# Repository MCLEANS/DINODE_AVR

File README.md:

# DINODE-AVR
An IOT development board based on ATMEGA32-16AU
        
        ATMEGA32-16AU DATASHEET
        http://ww1.microchip.com/downloads/en/devicedoc/doc2503.pdf

## BACKGROUND
The DINODE-AVR dev board comes out of the TU-K DATA open source project started by JACK MCLEANS and STEVE KIBUIKA from the Technical University of Kenya.
The project is intended to build a central database based on MongoDB with an API to insert data into and take data out of. 
The Central database is  to contain data from different IoT sensors from around the campus deployed by the students during their personal or final year projects.
By obtaining an API Key the various sensor data can be pushed to the database.
Projects that require data to implement such as Machine Learning and Data Visualization can also request for data from the "Data pool" and easily use it for their projects.

## CHALLENGE
A challenge arises where most of the students who do not have a hardware background or are just starting out do not have access to cheap internet enabled dev boards to start off.
Most of the available Internet Based Dev-boards are expensive or an option of modules such as WIFI and GSM which have "HARD" power requirements that are not easy for a beginer.
Most projects are also arduino based making students rely of third party libraries and abstracting them from the hardware. Arduino boards are also not suitable for realtime applicaions.

## Solution

As from the above challenges the DINODE-AVR was born, We decided to develop a Dev board based on the ATMEGA32 micro-controller with WIFI(ESP8266) and GSM connections already done,making in a plug and play for IoT one level lower than the ARDUINO to enable understanding of how the different IoT protocols work.

## VISION
To have more students get into Embedded systems and IoT development with a firm understanding of the basics.

# DINODE-AVR DEV-BOARD
The development board comes with an inbuilt user-led, user-potentiometer as well as "plug and play" sockets for LCD screen, ESP8266 and GSM SIM800L V2.0 to aid in IoT projects.

## LCD SCREEN PIN CONNECTIONS

        LCD       DINODE-AVR
        RS          PB0
        RW          PB1
        E           PB2
        D0          PC0
        D1          PC1
        D2          PC2
        D3          PC3
        D4          PC4
        D5          PC5
        D6          PC6
        D7          PC7
        A           +5V
        K           GND
        VSS         GND
        VDD         +5V

## USER-LED
The inbuilt USER-LED is connected to pin PD7 of the DINODE-AVR with a current limmiting resistor of 220 ohms

## USER-POTENTIOMETER
The user potentiometer is connected to pin PA0 of the DINODE-AVR

## ESP8266 CONNECTION

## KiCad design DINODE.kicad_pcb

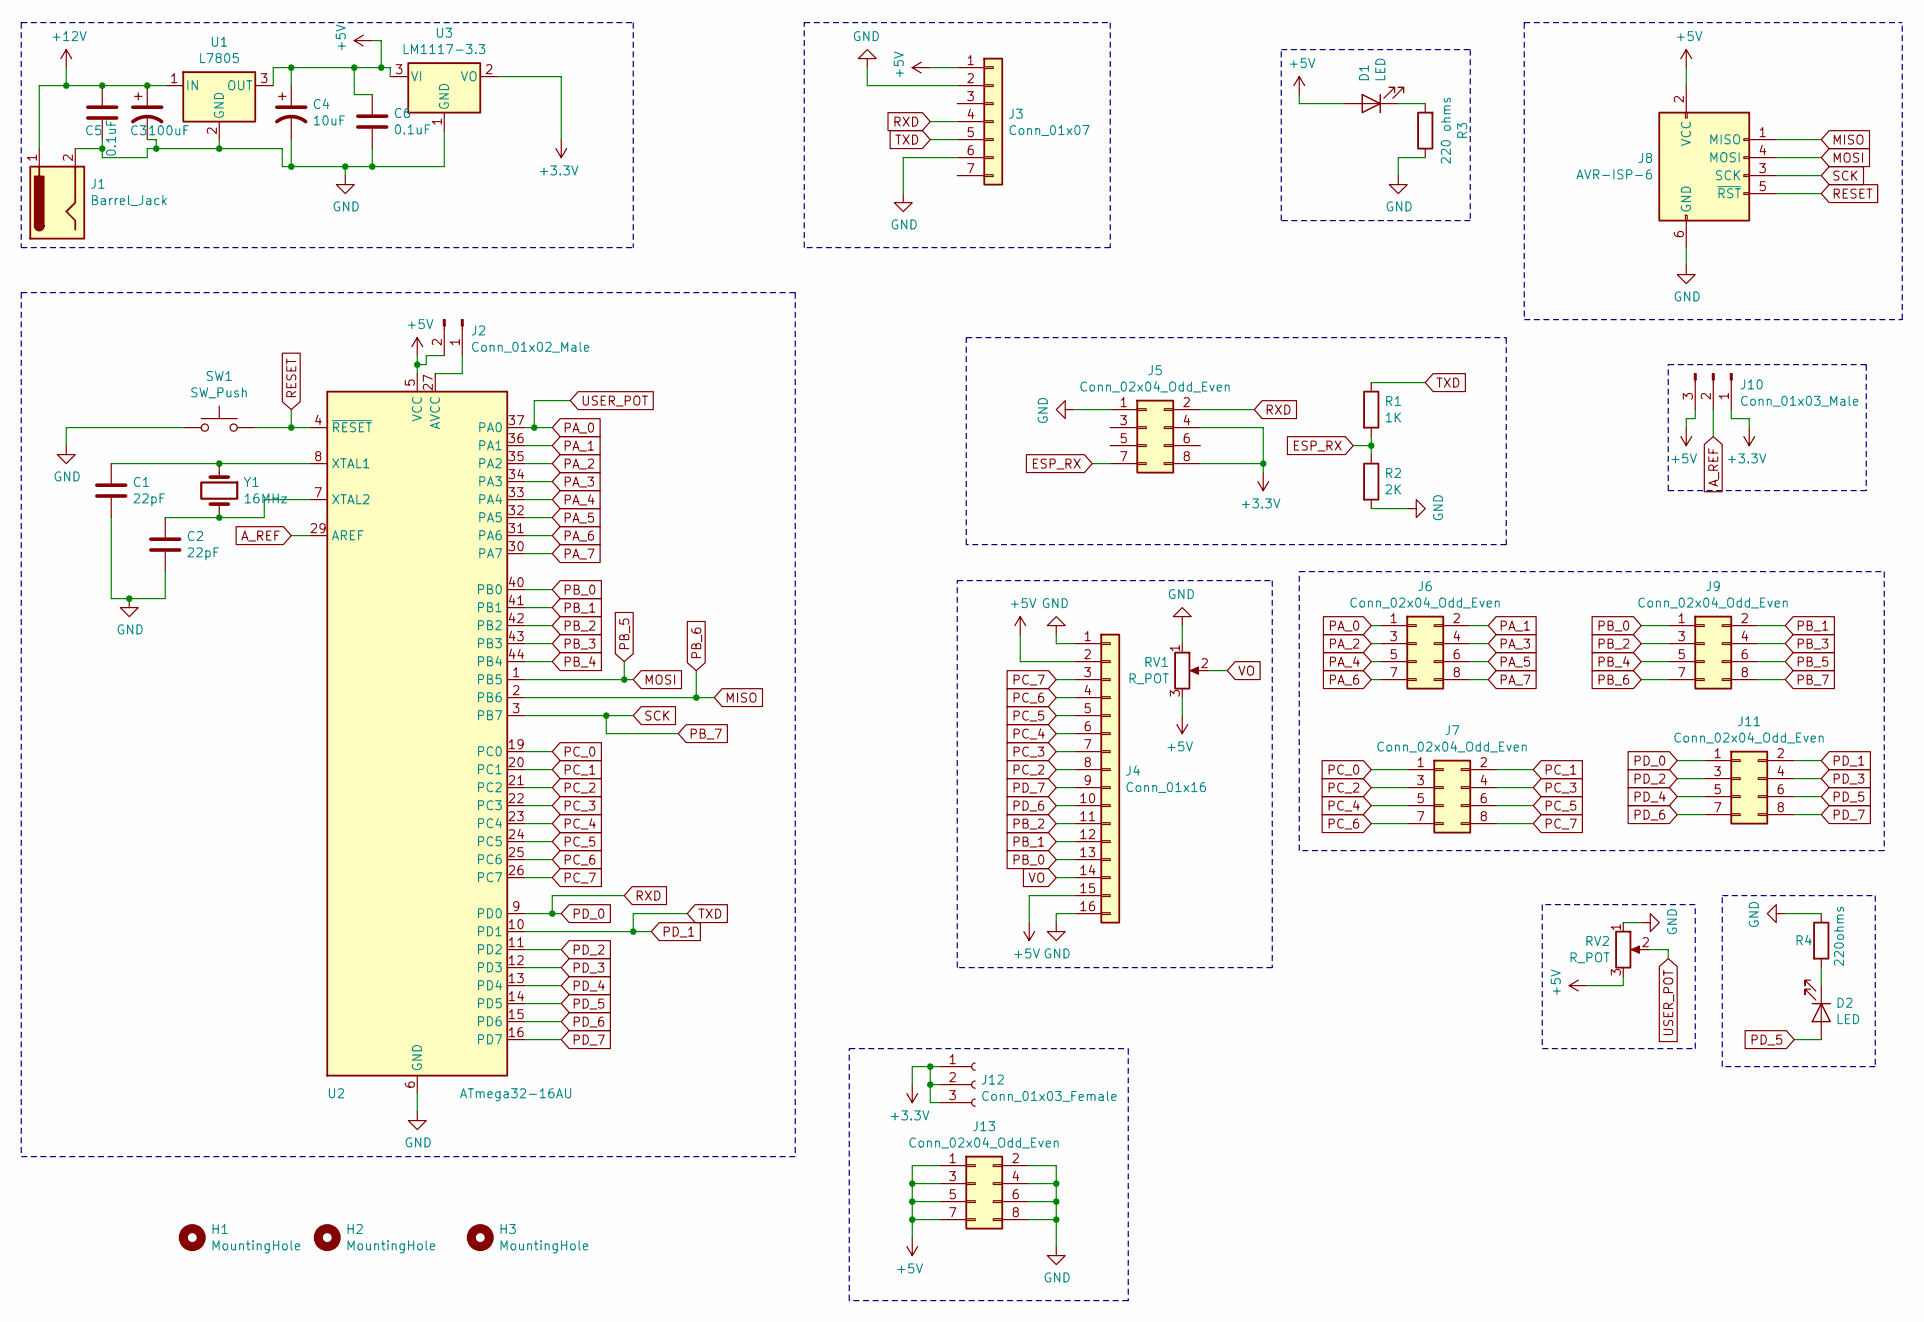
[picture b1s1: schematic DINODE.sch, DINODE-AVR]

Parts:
C1, C2: 22pF; C_0805_2012Metric
C3: 100uF; CP_Radial_D8.0mm_P5.00mm
C4: 10uF; CP_Radial_D8.0mm_P5.00mm
C5, C6: 0.1uF; C_0805_2012Metric
D1, D2: LED; LED_D3.0mm
H1, H2, H3: MountingHole; MountingHole_3.2mm_M3
J1: Barrel_Jack; BarrelJack_Horizontal
J2: Conn_01x02_Male; PinHeader_1x02_P2.54mm_Vertical
J3: Conn_01x07; PinSocket_1x07_P2.54mm_Vertical
J4: Conn_01x16; PinSocket_1x16_P2.54mm_Vertical
J5, J13: Conn_02x04_Odd_Even; PinSocket_2x04_P2.54mm_Vertical
J6, J7, J9, J11: Conn_02x04_Odd_Even; PinHeader_2x04_P2.54mm_Horizontal
J8: AVR-ISP-6; IDC-Header_2x03_P2.54mm_Horizontal
J10: Conn_01x03_Male; PinHeader_1x03_P2.54mm_Vertical
J12: Conn_01x03_Female; PinSocket_1x03_P2.54mm_Vertical
R1: 1K; R_Axial_DIN0207_L6.3mm_D2.5mm_P7.62mm_Horizontal
R2: 2K; R_Axial_DIN0207_L6.3mm_D2.5mm_P7.62mm_Horizontal
R3: 220 ohms; R_0805_2012Metric
R4: 220ohms; R_0805_2012Metric
RV1, RV2: R_POT; Potentiometer_Piher_PT-6-V_Vertical
SW1: SW_Push; SW_PUSH_6mm_H5mm
U1: L7805; TO-220-3
U2: ATmega32-16AU; TQFP-44_10x10mm_P0.8mm
U3: LM1117-3.3; SOT-223
Y1: 16MHz; Crystal_HC49-U_Vertical

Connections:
+3V3: J5.4, J5.8, J10.1, J12.1, J12.2, J12.3, U3.2 (VO)
+5V: C4.1, C6.1, D1.2 (A), J2.2, J3.1, J4.2, J4.15, J8.2 (VCC), J10.3, J13.1, J13.3, J13.5, J13.7, RV1.3, RV2.3, U1.3 (OUT), U2.5 (VCC), U2.17 (VCC), U2.38 (VCC), U3.3 (VI)
+12V: C3.1, C5.1, J1.1, U1.1 (IN)
A_REF: J10.2, U2.29 (AREF)
ESP_RX: J5.7, R1.2, R2.1
GND: C1.2, C2.2, C3.2, C4.2, C5.2, C6.2, J1.2, J3.2, J3.6, J4.1, J4.16, J5.1, J8.6 (GND), J13.2, J13.4, J13.6, J13.8, R2.2, R3.1, R4.1, RV1.1, RV2.1, SW1.1, U1.2 (GND), U2.6 (GND), U2.18 (GND), U2.28 (GND), U2.39 (GND), U3.1 (GND)
MISO: J8.1 (MISO), J9.7, U2.2 (PB6)
MOSI: J8.4 (MOSI), J9.6, U2.1 (PB5)
unnamed: C1.1, U2.8 (XTAL1), Y1.1
unnamed: C2.1, U2.7 (XTAL2), Y1.2
unnamed: D1.1 (K), R3.2
unnamed: D2.1 (K), R4.2
unnamed: J2.1, U2.27 (AVCC)
PA_0: J6.1, RV2.2, U2.37 (PA0)
PA_1: J6.2, U2.36 (PA1)
PA_2: J6.3, U2.35 (PA2)
PA_3: J6.4, U2.34 (PA3)
PA_4: J6.5, U2.33 (PA4)
PA_5: J6.6, U2.32 (PA5)
PA_6: J6.7, U2.31 (PA6)
PA_7: J6.8, U2.30 (PA7)
PB_0: J4.13, J9.1, U2.40 (PB0)
PB_1: J4.12, J9.2, U2.41 (PB1)
PB_2: J4.11, J9.3, U2.42 (PB2)
PB_3: J9.4, U2.43 (PB3)
PB_4: J9.5, U2.44 (PB4)
PB_7: J8.3 (SCK), J9.8, U2.3 (PB7)
PC_0: J7.1, U2.19 (PC0)
PC_1: J7.2, U2.20 (PC1)
PC_2: J4.8, J7.3, U2.21 (PC2)
PC_3: J4.7, J7.4, U2.22 (PC3)
PC_4: J4.6, J7.5, U2.23 (PC4)
PC_5: J4.5, J7.6, U2.24 (PC5)
PC_6: J4.4, J7.7, U2.25 (PC6)
PC_7: J4.3, J7.8, U2.26 (PC7)
PD_0: J3.4, J5.2, J11.1, U2.9 (PD0)
PD_1: J3.5, J11.2, R1.1, U2.10 (PD1)
PD_2: J11.3, U2.11 (PD2)
PD_3: J11.4, U2.12 (PD3)
PD_4: J11.5, U2.13 (PD4)
PD_5: D2.2 (A), J11.6, U2.14 (PD5)
PD_6: J4.10, J11.7, U2.15 (PD6)
PD_7: J4.9, J11.8, U2.16 (PD7)
RESET: J8.5 (~RST), SW1.2, U2.4 (~RESET)
VO: J4.14, RV1.2

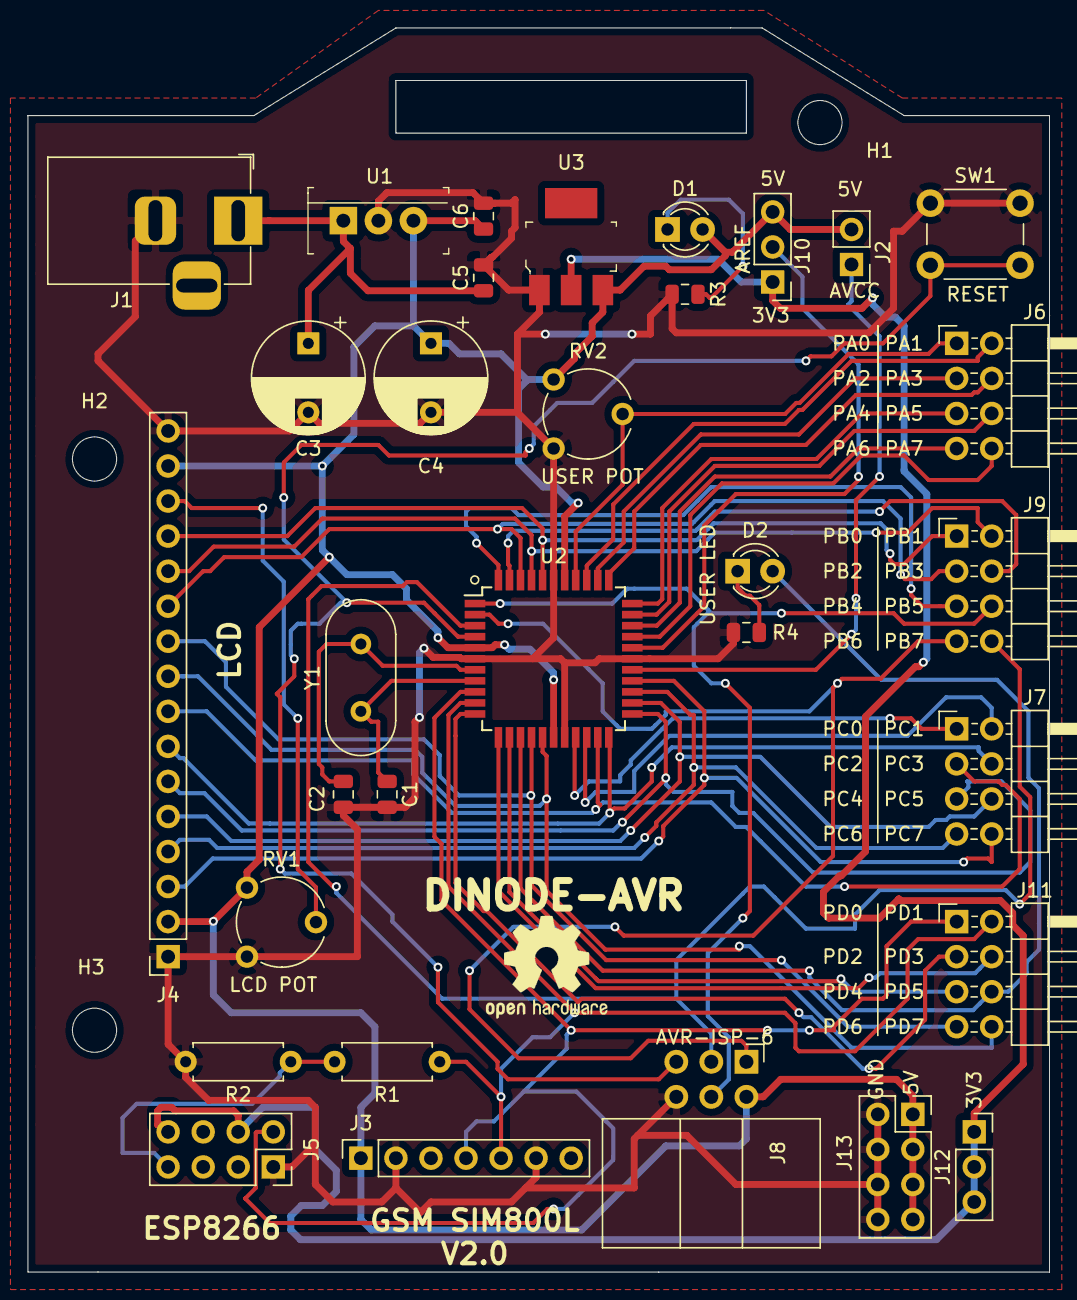
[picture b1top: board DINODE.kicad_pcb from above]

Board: 2 copper layers, 74.0 x 90.2 mm, 35 parts (0 on the bottom side), 45 nets.

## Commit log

2019-11-15 KICAD BOARD FILES
2019-11-17 Create README.md
    project documentation
2019-11-18 Addition of esp8266 connection to the circuit
2019-11-21 updated LCD layout
2019-11-22 Updated circuit footprints
2019-11-22 Addition of LCD, USER-LED and USER-POTENTIOMETER pin layout to documentation
2019-11-22 Updated push_button from 4.3mm to 5mm
2019-11-22 Updated design
2019-11-23 Updated power led position
2019-11-24 Included esp8266 documentation
2019-11-27 Started routing
2019-11-27 Port C routing
2019-11-27 Completed Routing
2019-12-07 Addition of edge cuts
2019-12-10 Addition of open-source logo
2019-12-10 Addition of dev-board photo
2019-12-10 Addition of dev-board image to documentation
2019-12-10 updated image on documentation
2019-12-10 updated documentation
2020-01-08 updated edge cuts and copper fill zones
2020-01-08 updated schematic capture
2020-01-08 Updated board image
2020-01-10 Added gerber files
2020-01-10 updated gerber files
2020-01-11 production files with BOM
